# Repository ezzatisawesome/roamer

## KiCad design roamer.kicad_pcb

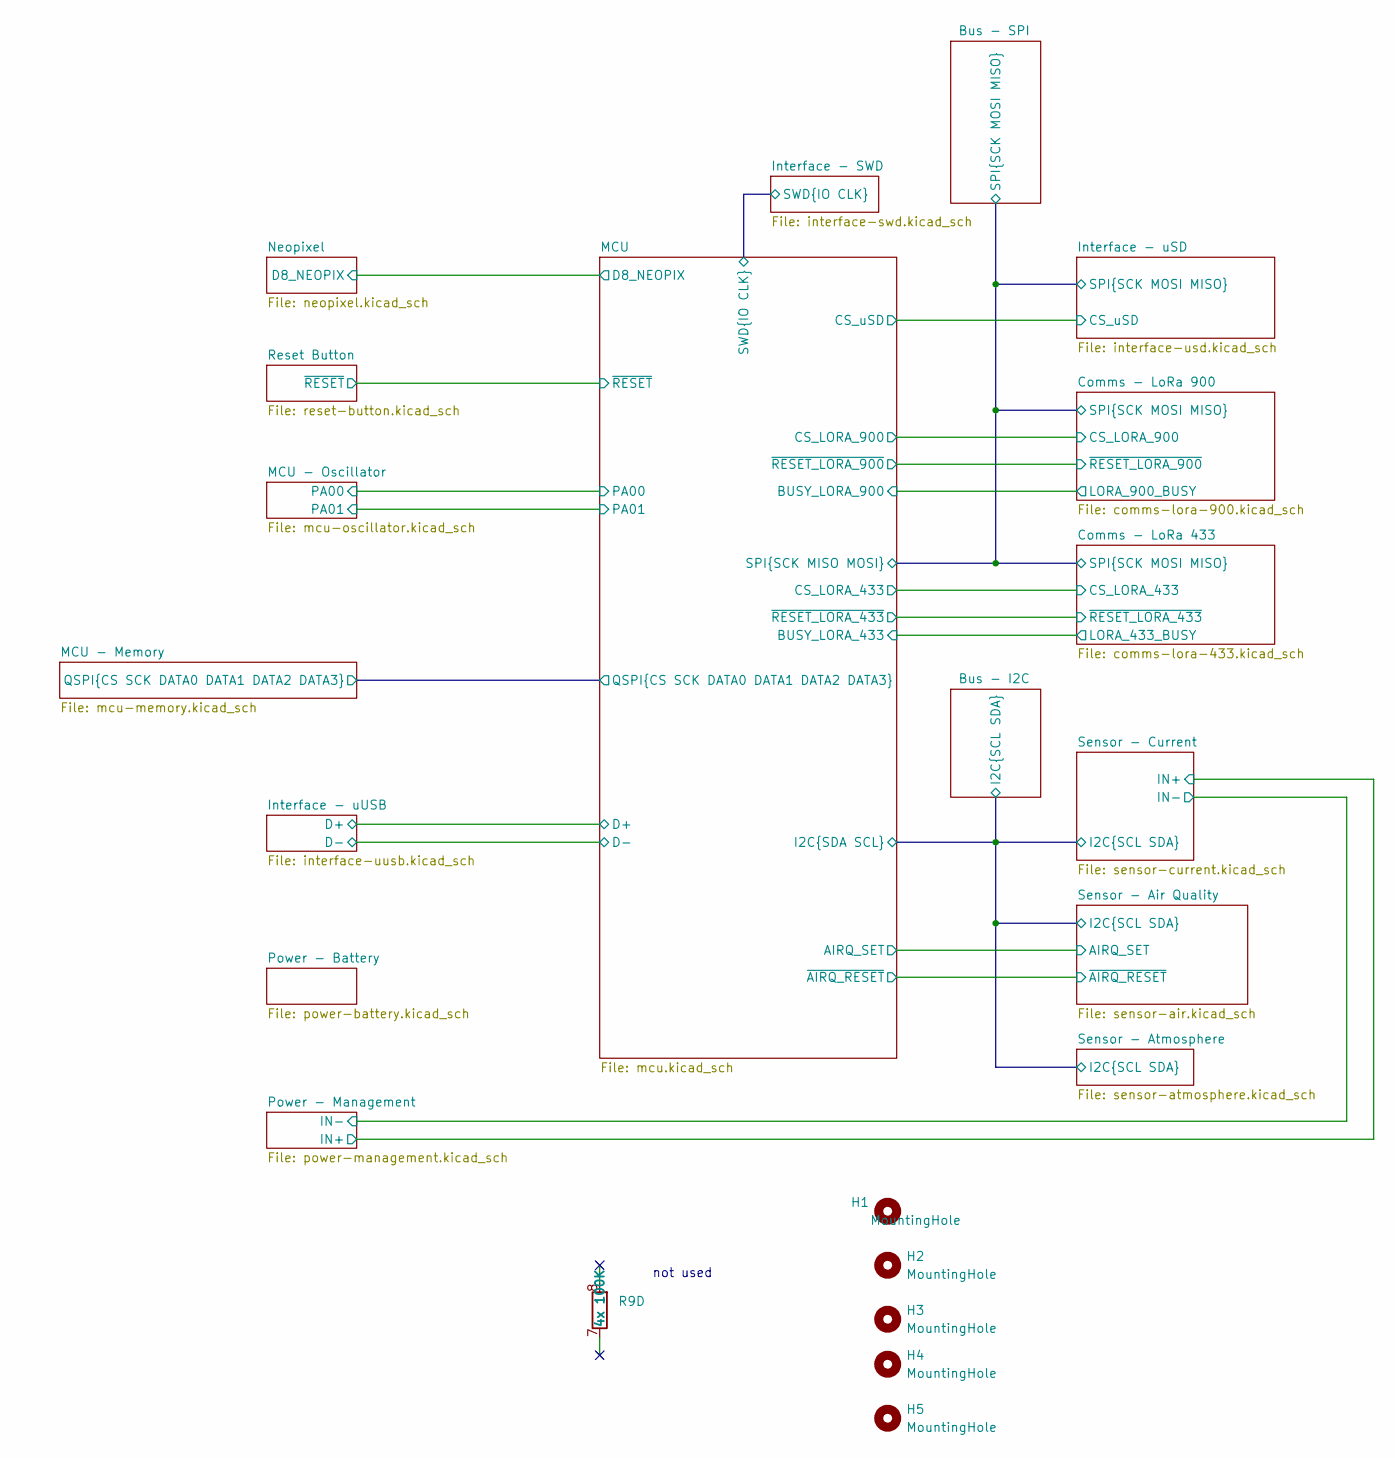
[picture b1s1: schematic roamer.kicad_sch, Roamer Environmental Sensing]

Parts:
H1, H2, H3, H4, H5: MountingHole; MountingHole_2.2mm_M2_DIN965_Pad
R9: 4x 100K; R_Array_Convex_4x1206; Mfr P/N CAY16-1003F4LF

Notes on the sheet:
not used

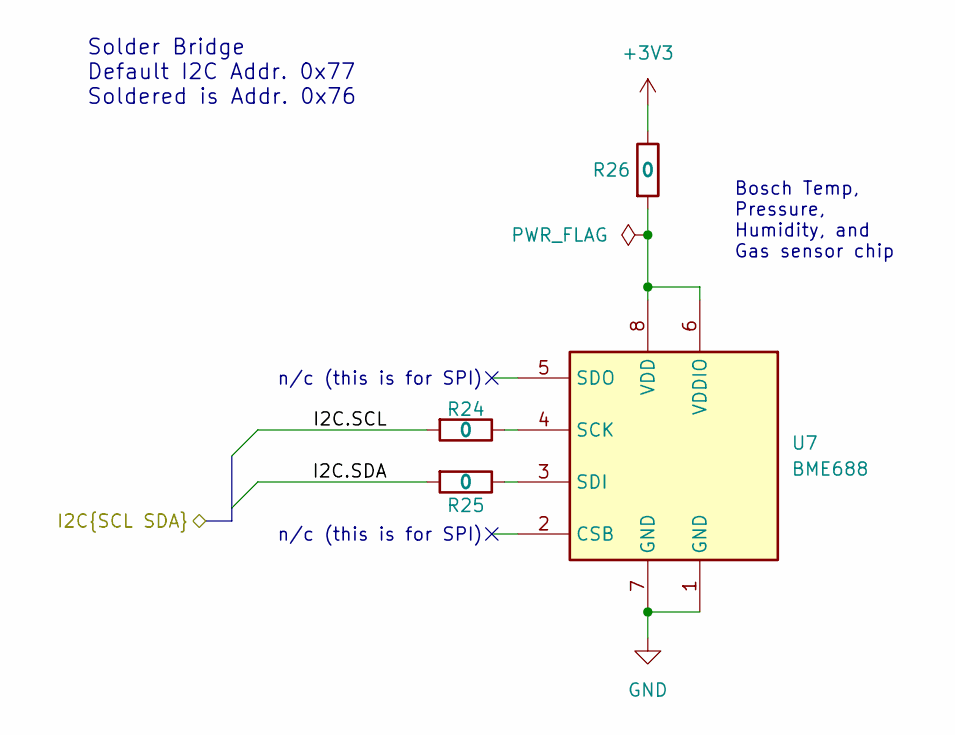
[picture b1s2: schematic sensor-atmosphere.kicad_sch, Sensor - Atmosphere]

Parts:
R24, R25, R26: 0; R_0603_1608Metric; Mfr P/N RC0603JR-070RL
U7: BME688; Bosch_LGA-8_3x3mm_P0.8mm_ClockwisePinNumbering; Mfr P/N BME688

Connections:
+3V3: R26.1; also elsewhere on the board
/Bus - I2C/I2C.SCL: R24.2; also elsewhere on the board
/Bus - I2C/I2C.SDA: R25.2; also elsewhere on the board
GND: U7.1 (GND), U7.7 (GND); also elsewhere on the board
unnamed: R24.1, U7.4 (SCK)
unnamed: R25.1, U7.3 (SDI)
unnamed: R26.2, U7.6 (VDDIO), U7.8 (VDD)

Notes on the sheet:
n/c (this is for SPI)
Bosch Temp, Pressure, Humidity, and Gas sensor chip
Solder Bridge Default I2C Addr. 0x77 Soldered is Addr. 0x76

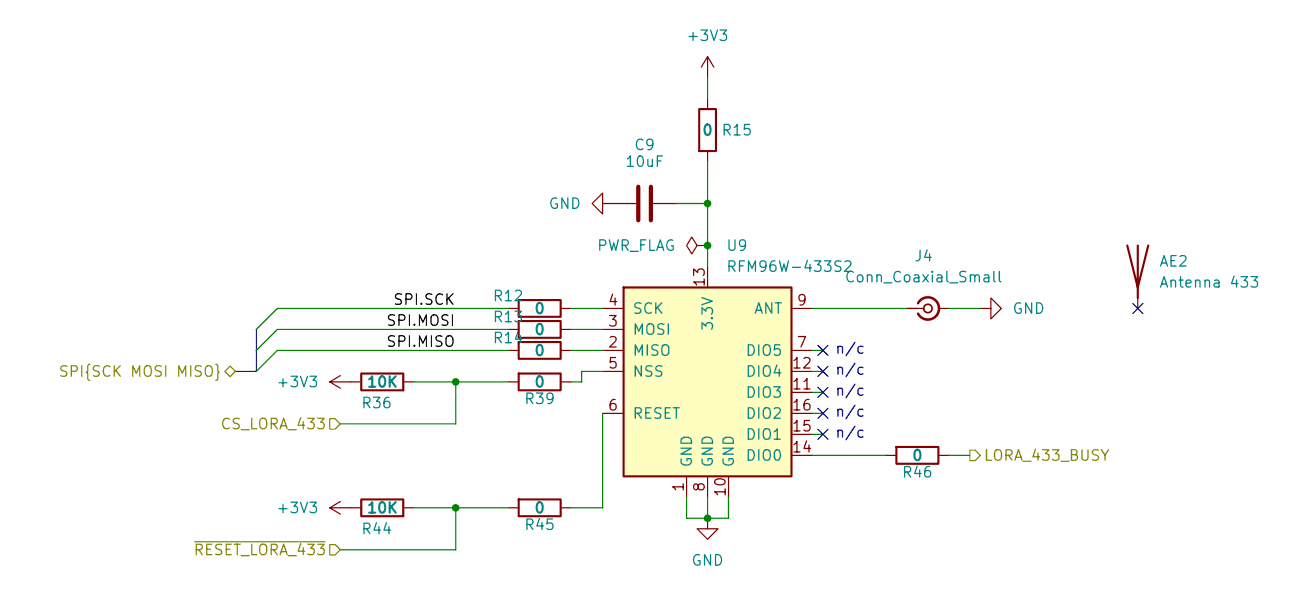
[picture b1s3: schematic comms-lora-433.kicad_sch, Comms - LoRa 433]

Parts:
AE2: Antenna 433; Mfr P/N ANT-433-PW-QW-UFL
C9: 10uF; L_0805_2012Metric; Mfr P/N CL21A106KOQNNNE
J4: Conn_Coaxial_Small; U.FL_Molex_MCRF_73412-0110_Vertical; Mfr P/N 0734120110
R12, R13, R14, R15, R39, R45, R46: 0; R_0603_1608Metric; Mfr P/N RC0603JR-070RL
R36, R44: 10K; R_0603_1608Metric; Mfr P/N RNCP0603FTD10K0
U9: RFM96W-433S2; HOPERF_RFM9XW_SMD; Mfr P/N 3073

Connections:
+3V3: R15.1, R36.1, R44.1; also elsewhere on the board
/Bus - SPI/SPI.MISO: R14.2; also elsewhere on the board
/Bus - SPI/SPI.MOSI: R13.2; also elsewhere on the board
/Bus - SPI/SPI.SCK: R12.2; also elsewhere on the board
/Comms - LoRa 433/CS_LORA_433: R36.2, R39.2; also elsewhere on the board
/Comms - LoRa 433/LORA_433_BUSY: R46.1; also elsewhere on the board
/Comms - LoRa 433/~RESET_LORA_433: R44.2, R45.2; also elsewhere on the board
GND: C9.1, J4.2 (Ext), U9.1 (GND), U9.8 (GND), U9.10 (GND); also elsewhere on the board
unnamed: J4.1 (In), U9.9 (ANT)
unnamed: C9.2, R15.2, U9.13 (3.3V)
unnamed: R46.2, U9.14 (DIO0)
unnamed: R14.1, U9.2 (MISO)
unnamed: R13.1, U9.3 (MOSI)
unnamed: R39.1, U9.5 (NSS)
unnamed: R45.1, U9.6 (RESET)
unnamed: R12.1, U9.4 (SCK)

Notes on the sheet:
n/c

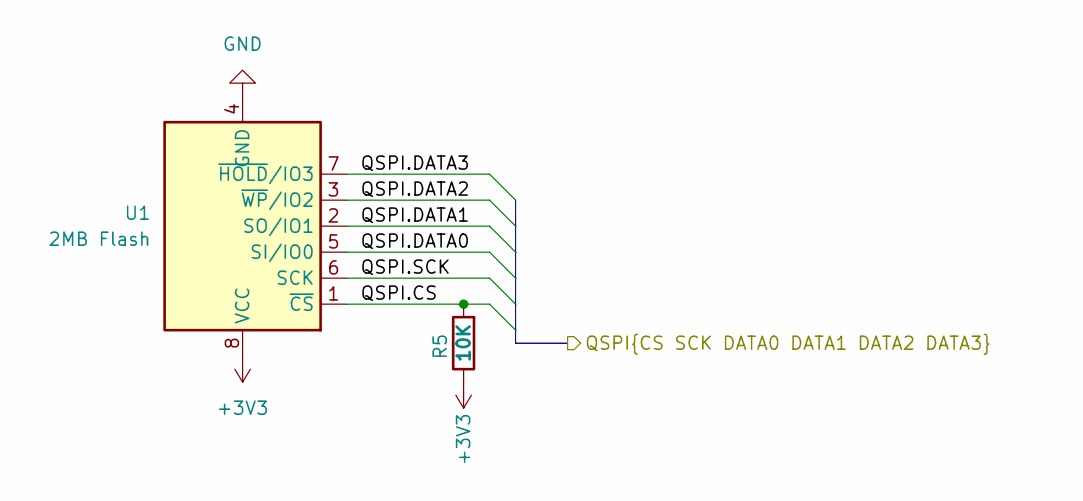
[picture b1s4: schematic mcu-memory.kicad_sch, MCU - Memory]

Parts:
R5: 10K; R_0603_1608Metric; Mfr P/N RNCP0603FTD10K0
U1: 2MB Flash; SOIC-8_3.9x4.9mm_P1.27mm; Mfr P/N GD25Q16ETIGR

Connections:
+3V3: R5.1, U1.8 (VCC); also elsewhere on the board
/MCU - Memory/QSPI.CS: R5.2, U1.1 (~CS); also elsewhere on the board
/MCU - Memory/QSPI.DATA0: U1.5 (SI/IO0); also elsewhere on the board
/MCU - Memory/QSPI.DATA1: U1.2 (SO/IO1); also elsewhere on the board
/MCU - Memory/QSPI.DATA2: U1.3 (~WP/IO2); also elsewhere on the board
/MCU - Memory/QSPI.DATA3: U1.7 (~HOLD/IO3); also elsewhere on the board
/MCU - Memory/QSPI.SCK: U1.6 (SCK); also elsewhere on the board
GND: U1.4 (GND); also elsewhere on the board

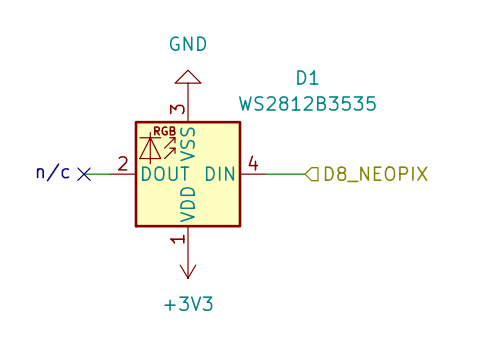
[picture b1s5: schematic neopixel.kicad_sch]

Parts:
D1: WS2812B3535; LED_SK6812MINI_PLCC4_3.5x3.5mm_P1.75mm; Mfr P/N SK6812MINI

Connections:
+3V3: D1.1 (VDD); also elsewhere on the board
/MCU/D8_NEOPIX: D1.4 (DIN); also elsewhere on the board
GND: D1.3 (VSS); also elsewhere on the board

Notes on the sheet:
n/c

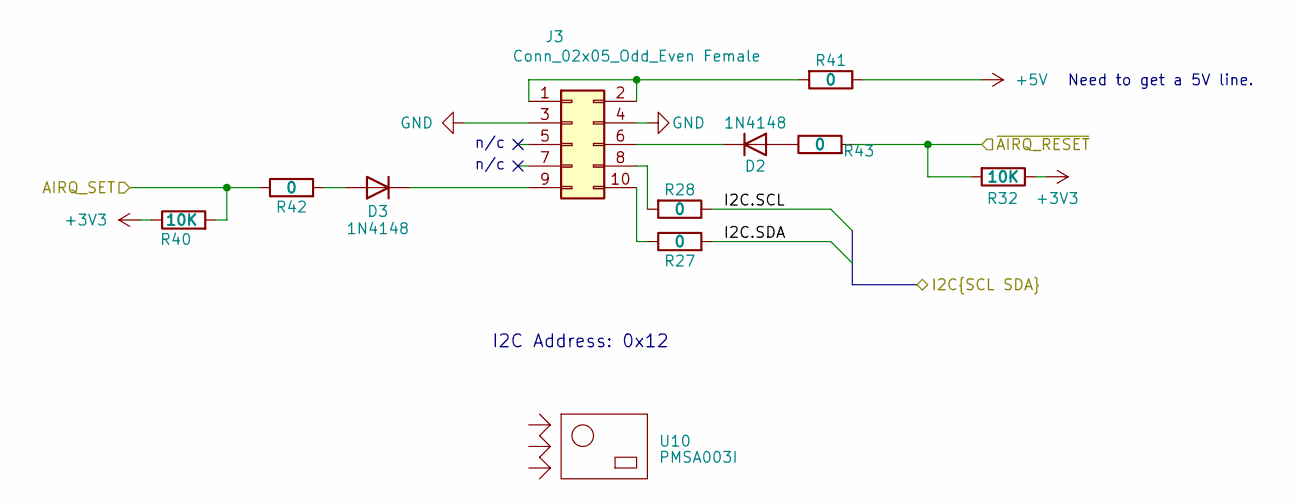
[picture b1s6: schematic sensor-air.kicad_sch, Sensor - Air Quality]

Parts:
D2, D3: 1N4148; D_SOD-323F; Mfr P/N 1N4148WX-TP
J3: Conn_02x05_Odd_Even Female; PinHeader_2x05_P1.27mm_Vertical_SMD; Mfr P/N 20021321-00010C4LF
R27, R28, R41, R42, R43: 0; R_0603_1608Metric; Mfr P/N RC0603JR-070RL
R32, R40: 10K; R_0603_1608Metric; Mfr P/N RNCP0603FTD10K0
U10: PMSA003I; Mfr P/N ZIO-101962

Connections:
+3V3: R32.1, R40.1; also elsewhere on the board
+5V: R41.1; also elsewhere on the board
/Bus - I2C/I2C.SCL: R28.1; also elsewhere on the board
/Bus - I2C/I2C.SDA: R27.2; also elsewhere on the board
/MCU/AIRQ_SET: R40.2, R42.1; also elsewhere on the board
/MCU/~AIRQ_RESET: R32.2, R43.2; also elsewhere on the board
GND: J3.3, J3.4; also elsewhere on the board
unnamed: D2.2 (A), R43.1
unnamed: D2.1 (K), J3.6
unnamed: D3.2 (A), R42.2
unnamed: D3.1 (K), J3.9
unnamed: J3.1, J3.2, R41.2
unnamed: J3.8, R28.2
unnamed: J3.10, R27.1

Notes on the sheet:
n/c
Need to get a 5V line.
I2C Address: 0x12

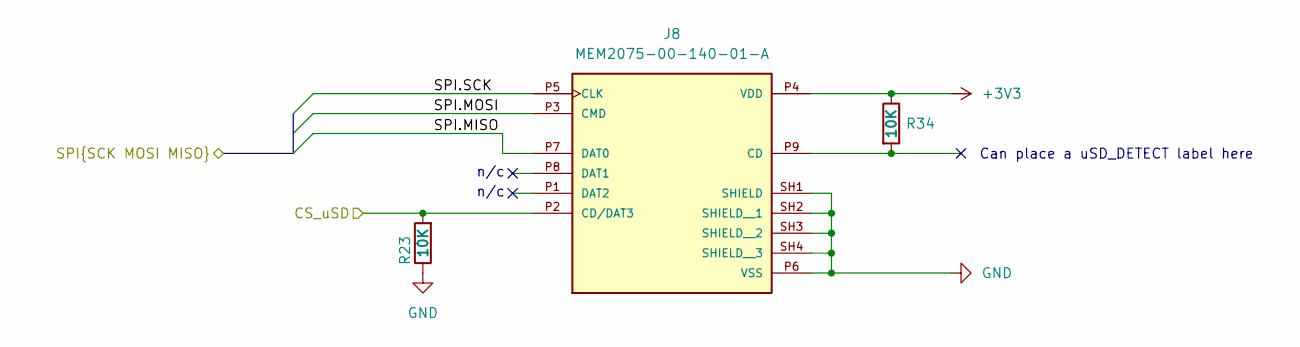
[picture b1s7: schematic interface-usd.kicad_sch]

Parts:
J8: MEM2075-00-140-01-A; GCT_MEM2075-00-140-01-A; PARTREV A
R23, R34: 10K; R_0603_1608Metric; Mfr P/N RNCP0603FTD10K0

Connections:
+3V3: J8.P4 (VDD), R34.1; also elsewhere on the board
/Bus - SPI/SPI.MISO: J8.P7 (DAT0); also elsewhere on the board
/Bus - SPI/SPI.MOSI: J8.P3 (CMD); also elsewhere on the board
/Bus - SPI/SPI.SCK: J8.P5 (CLK); also elsewhere on the board
/Interface - uSD/CS_uSD: J8.P2 (CD/DAT3), R23.2; also elsewhere on the board
GND: J8.P6 (VSS), J8.SH1 (SHIELD), J8.SH2 (SHIELD__1), J8.SH3 (SHIELD__2), J8.SH4 (SHIELD__3), R23.1; also elsewhere on the board

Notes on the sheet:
Can place a uSD_DETECT label here
n/c

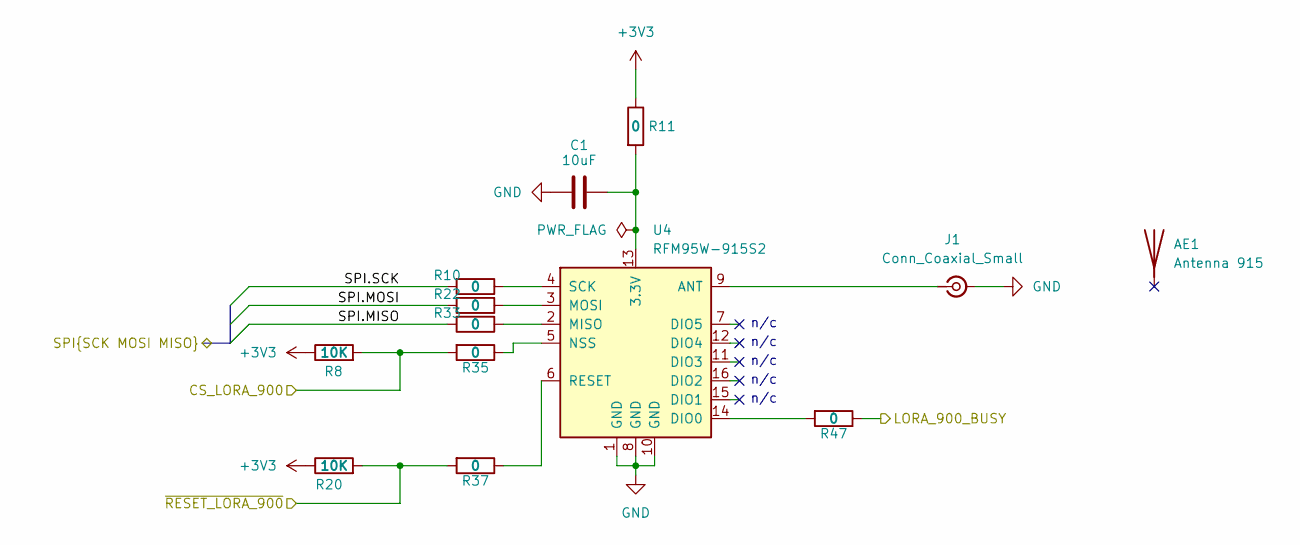
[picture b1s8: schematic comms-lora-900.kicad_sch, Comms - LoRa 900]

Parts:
AE1: Antenna 915; Mfr P/N ANT-916-PW-QW-UFL
C1: 10uF; L_0805_2012Metric; Mfr P/N CL21A106KOQNNNE
J1: Conn_Coaxial_Small; U.FL_Molex_MCRF_73412-0110_Vertical; Mfr P/N 0734120110
R8, R20: 10K; R_0603_1608Metric; Mfr P/N RNCP0603FTD10K0
R10, R11, R22, R33, R35, R37, R47: 0; R_0603_1608Metric; Mfr P/N RC0603JR-070RL
U4: RFM95W-915S2; HOPERF_RFM9XW_SMD; Mfr P/N 3072

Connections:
+3V3: R8.1, R11.1, R20.1; also elsewhere on the board
/Bus - SPI/SPI.MISO: R33.2; also elsewhere on the board
/Bus - SPI/SPI.MOSI: R22.2; also elsewhere on the board
/Bus - SPI/SPI.SCK: R10.2; also elsewhere on the board
/Comms - LoRa 900/CS_LORA_900: R8.2, R35.2; also elsewhere on the board
/Comms - LoRa 900/LORA_900_BUSY: R47.1; also elsewhere on the board
/Comms - LoRa 900/~RESET_LORA_900: R20.2, R37.2; also elsewhere on the board
GND: C1.1, J1.2 (Ext), U4.1 (GND), U4.8 (GND), U4.10 (GND); also elsewhere on the board
unnamed: J1.1 (In), U4.9 (ANT)
unnamed: C1.2, R11.2, U4.13 (3.3V)
unnamed: R47.2, U4.14 (DIO0)
unnamed: R33.1, U4.2 (MISO)
unnamed: R22.1, U4.3 (MOSI)
unnamed: R35.1, U4.5 (NSS)
unnamed: R37.1, U4.6 (RESET)
unnamed: R10.1, U4.4 (SCK)

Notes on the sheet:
n/c

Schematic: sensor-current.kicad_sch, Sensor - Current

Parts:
C19: 1uF; C_0603_1608Metric; Mfr P/N CC0603KRX7R7BB105
R16, R17, R18, R19, R21: 0; R_0603_1608Metric; Mfr P/N RC0603JR-070RL
U8: INA260; TSSOP-16_4.4x5mm_P0.65mm; Mfr P/N INA260AIPWR

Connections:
+3V3: R18.2; also elsewhere on the board
+BATT: R19.2; also elsewhere on the board
/Bus - I2C/I2C.SCL: R16.1; also elsewhere on the board
/Bus - I2C/I2C.SDA: R17.1; also elsewhere on the board
/Power - Management/IN-: R21.2; also elsewhere on the board
GND: C19.2, U8.6 (GND), U8.11 (GND); also elsewhere on the board
unnamed: R21.1, U8.14 (IN-), U8.15 (IN-), U8.16 (IN-)
unnamed: R16.2, U8.9 (SCL)
unnamed: R17.2, U8.8 (SDA)
unnamed: R19.1, U8.1 (IN+), U8.2 (IN+), U8.3 (IN+), U8.12 (VBUS)
unnamed: C19.1, R18.1, U8.10 (VS)

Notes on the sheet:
A1 A0 I2C Address (hex) GND GND 0x40(Default) GND VCC 0x41 VCC GND 0x44 VCC VCC 0x45
n/c

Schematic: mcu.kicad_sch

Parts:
C13: 10uF; L_0805_2012Metric; Mfr P/N CL21A106KOQNNNE
C14, C15: 1uF; C_0603_1608Metric; Mfr P/N CC0603KRX7R7BB105
JP1: SolderJumper_2_Open; SolderJumper-2_P1.3mm_Open_TrianglePad1.0x1.5mm
L1: RED; LED_0805_2012Metric; Mfr P/N LTST-S220KRKT
L2: 10uH; L_1008_2520Metric; Mfr P/N LSQEA251818T100K
MCU1: ATSAMD51J19A-A; TQFP-64_10x10mm_P0.5mm; Mfr P/N ATSAMD51J19A-AUTCT-ND
R6: 10K; R_0603_1608Metric; Mfr P/N RNCP0603FTD10K0
R7: 2.2K; R_0603_1608Metric; Mfr P/N CRGH0603F2K2
R9: 4x 100K; R_Array_Convex_4x1206; Mfr P/N CAY16-1003F4LF

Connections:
+3V3: JP1.2 (B), MCU1.8 (VDDANA), MCU1.16 (PA07), MCU1.21 (VDDIOB), MCU1.34 (VDDIO), MCU1.48 (VDDIO), MCU1.56 (VDDIO), R6.1; also elsewhere on the board
+BATT: R9.2 (R1.2); also elsewhere on the board
/Bus - I2C/I2C.SCL: MCU1.30 (PA13); also elsewhere on the board
/Bus - I2C/I2C.SDA: MCU1.29 (PA12); also elsewhere on the board
/Bus - SPI/SPI.MISO: MCU1.49 (PB22); also elsewhere on the board
/Bus - SPI/SPI.MOSI: MCU1.50 (PB23); also elsewhere on the board
/Bus - SPI/SPI.SCK: MCU1.36 (PA17); also elsewhere on the board
/Comms - LoRa 433/CS_LORA_433: MCU1.35 (PA16); also elsewhere on the board
/Comms - LoRa 433/LORA_433_BUSY: MCU1.40 (PB17); also elsewhere on the board
/Comms - LoRa 433/~RESET_LORA_433: MCU1.41 (PA20); also elsewhere on the board
/Comms - LoRa 900/CS_LORA_900: MCU1.31 (PA14); also elsewhere on the board
/Comms - LoRa 900/LORA_900_BUSY: MCU1.39 (PB16); also elsewhere on the board
/Comms - LoRa 900/~RESET_LORA_900: MCU1.38 (PA19); also elsewhere on the board
/Interface - SWD/SWD.CLK: MCU1.57 (PA30), R6.2; also elsewhere on the board
/Interface - SWD/SWD.IO: MCU1.58 (PA31); also elsewhere on the board
/Interface - uSD/CS_uSD: MCU1.37 (PA18); also elsewhere on the board
/Interface - uUSB/D+: MCU1.46 (PA25); also elsewhere on the board
/Interface - uUSB/D-: MCU1.45 (PA24); also elsewhere on the board
/MCU - Memory/QSPI.CS: MCU1.24 (PB11); also elsewhere on the board
/MCU - Memory/QSPI.DATA0: MCU1.17 (PA08); also elsewhere on the board
/MCU - Memory/QSPI.DATA1: MCU1.18 (PA09); also elsewhere on the board
/MCU - Memory/QSPI.DATA2: MCU1.19 (PA10); also elsewhere on the board
/MCU - Memory/QSPI.DATA3: MCU1.20 (PA11); also elsewhere on the board
/MCU - Memory/QSPI.SCK: MCU1.23 (PB10); also elsewhere on the board
/MCU - Oscillator/PA00: MCU1.1 (PA00); also elsewhere on the board
/MCU - Oscillator/PA01: MCU1.2 (PA01); also elsewhere on the board
/MCU/AIRQ_SET: MCU1.43 (PA22); also elsewhere on the board
/MCU/AREF: C14.1, JP1.1 (A), MCU1.4 (PA03); also elsewhere on the board
/MCU/D8_NEOPIX: MCU1.64 (PB03); also elsewhere on the board
/MCU/~AIRQ_RESET: MCU1.42 (PA21); also elsewhere on the board
/MCU/~RESET: MCU1.52 (~RESET); also elsewhere on the board
GND: C13.2, C14.2, C15.1, L1.1 (K), MCU1.7 (GNDANA), MCU1.22 (GND), MCU1.33 (GND), MCU1.47 (GND), MCU1.54 (GND), R9.3 (R2.1); also elsewhere on the board
unnamed: L1.2 (A), R7.1
unnamed: MCU1.44 (PA23), R7.2
unnamed: MCU1.62 (PB01), R9.1 (R1.1), R9.4 (R2.2)
unnamed: L2.2, MCU1.53 (VDDCORE)
unnamed: C13.1, C15.2, L2.1, MCU1.55 (VSW)

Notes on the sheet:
n/c
SWD PORT
RED INDICATOR LED

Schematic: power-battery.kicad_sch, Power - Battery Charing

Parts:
C3: 10uF; L_0805_2012Metric; Mfr P/N CL21A106KOQNNNE
CHG1: ORANGE; LED_0805_2012Metric; Mfr P/N B1701UD--20D000414U1930
J2: JSTPH; JST_PH_S2B-PH-SM4-TB_1x02-1MP_P2.00mm_Horizontal; Mfr P/N S2B-PH-SM4-TB
R2: 1K; C_0603_1608Metric; Mfr P/N MCT06030C1001FP500
R4: 10K; R_0603_1608Metric; Mfr P/N RNCP0603FTD10K0
U3: MCP73831-2-OT; SOT-23-5; Mfr P/N MCP73831T-2ATI/OT

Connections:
+BATT: C3.1, J2.1, U3.3 (V_{BAT}); also elsewhere on the board
GND: C3.2, J2.2, R4.1, U3.2 (V_{SS}); also elsewhere on the board
unnamed: CHG1.1 (K), R2.2
unnamed: R4.2, U3.5 (PROG)
unnamed: R2.1, U3.1 (STAT)
VBUS: CHG1.2 (A), U3.4 (V_{DD}); also elsewhere on the board

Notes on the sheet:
10K = 100mA 5.0K = 200mA 2.0K = 500mA 1.0K = 1000mA
ORGANGE CHARGING INDICATOR LED

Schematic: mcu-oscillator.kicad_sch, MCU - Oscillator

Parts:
C2, C4: 22pF; C_0603_1608Metric; Mfr P/N C0603C220K4GAC7867
X2: 32.768 kHz; Crystal_SMD_3215-2Pin_3.2x1.5mm; Mfr P/N STDMUA17-32.768K

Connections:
/MCU - Oscillator/PA00: C4.1, X2.1; also elsewhere on the board
/MCU - Oscillator/PA01: C2.1, X2.2; also elsewhere on the board
GND: C2.2, C4.2; also elsewhere on the board

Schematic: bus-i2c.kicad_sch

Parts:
R30, R31: 10K; R_0603_1608Metric; Mfr P/N RNCP0603FTD10K0

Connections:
+3V3: R30.1, R31.1; also elsewhere on the board
/Bus - I2C/I2C.SCL: R31.2; also elsewhere on the board
/Bus - I2C/I2C.SDA: R30.2; also elsewhere on the board

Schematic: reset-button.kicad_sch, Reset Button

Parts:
C12: 1uF; C_0603_1608Metric; Mfr P/N CC0603KRX7R7BB105
R1: 10K; R_0603_1608Metric; Mfr P/N RNCP0603FTD10K0
SW1: KMR2; SW_Push_1P1T_NO_CK_KMR2; Mfr P/N KM241NG ULC LFS

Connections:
+3V3: R1.2; also elsewhere on the board
/MCU/~RESET: C12.1, R1.1, SW1.2; also elsewhere on the board
GND: C12.2, SW1.1; also elsewhere on the board

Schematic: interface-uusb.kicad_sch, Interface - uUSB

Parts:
TP3: D+ Testpoint; TestPoint_Pad_D1.0mm
TP4: D- TestPoint; TestPoint_Pad_D1.0mm
X3: microUSB 2.0 B; USB_Micro-B_Amphenol_10118194_Horizontal; Mfr P/N 10118194-0001LF

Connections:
/Interface - uUSB/D+: TP3.1, X3.3 (D+); also elsewhere on the board
/Interface - uUSB/D-: TP4.1, X3.2 (D-); also elsewhere on the board
GND: X3.5 (GND), X3.6 (Shield); also elsewhere on the board
VBUS: X3.1 (VBUS); also elsewhere on the board

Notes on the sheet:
n/c

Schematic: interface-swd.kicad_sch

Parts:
J5: Conn_02x05_Odd_Even Male; PinHeader_2x05_P1.27mm_Vertical_SMD; Mfr P/N 3220-10-0300-00

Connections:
+3V3: J5.1; also elsewhere on the board
/Interface - SWD/Key: J5.7
/Interface - SWD/SWD.CLK: J5.4; also elsewhere on the board
/Interface - SWD/SWD.IO: J5.2; also elsewhere on the board
/Interface - SWD/SWO: J5.6
/Interface - SWD/n/c: J5.8
/Interface - SWD/~RST: J5.10
GND: J5.3, J5.5, J5.9; also elsewhere on the board

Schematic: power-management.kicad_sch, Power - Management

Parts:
C5, C6, C8, C16, C17: 10uF; L_0805_2012Metric; Mfr P/N CL21A106KOQNNNE
C7, C10, C11, C18: 1uF; C_0603_1608Metric; Mfr P/N CC0603KRX7R7BB105
D4: MBR120; D_SOD-123; Mfr P/N MBR120LSFT1G
JP3: SolderJumper_2_Open; SolderJumper-2_P1.3mm_Open_TrianglePad1.0x1.5mm
Q3: DMP2070UQ-7; TSOT-23; Mfr P/N DMP2070UQ-7
R3: 10K; R_0603_1608Metric; Mfr P/N RNCP0603FTD10K0
R9: 4x 100K; R_Array_Convex_4x1206; Mfr P/N CAY16-1003F4LF
R38: 100K; R_0805_2012Metric; Mfr P/N RC0805FR-07100KL
TP1: VBUS Testpoint; TestPoint_Loop_D2.50mm_Drill1.0mm; Mfr P/N 5001
TP2: Batt Testpoint; TestPoint_Loop_D2.50mm_Drill1.0mm; Mfr P/N 5001
TP5: 5V Testpoint; TestPoint_Loop_D2.50mm_Drill1.0mm; Mfr P/N 5001
TP6: GND Testpoint; TestPoint_Loop_D2.50mm_Drill1.0mm; Mfr P/N 5001
TP7: 3V3 Testpoint; TestPoint_Loop_D2.50mm_Drill1.0mm; Mfr P/N 5001
U2: AP2112K-3.3; SOT-23-5; Mfr P/N AP2112K-3.3TRG1
U6: AP3602AKTR-G1; SOT-23-6_DIO; Mfr P/N AP3602AKTR-G1

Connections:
+3V3: C5.1, C7.1, C8.1, C10.2, C11.2, TP7.1, U2.5 (VOUT); also elsewhere on the board
+5V: C16.1, TP5.1, U6.1 (VOUT); also elsewhere on the board
/Power - Management/IN-: JP3.1 (A), Q3.1 (D); also elsewhere on the board
/Power - Management/POWER_IN: C6.1, C17.1, D4.1 (K), Q3.3 (S), R3.1, R38.2, U2.1 (VIN), U6.5 (VIN)
GND: C5.2, C6.2, C7.2, C8.2, C10.1, C11.1, C16.2, C17.2, R9.5 (R3.1), TP6.1, U2.2 (GND), U6.2 (GND); also elsewhere on the board
unnamed: JP3.2 (B), TP2.1
unnamed: R3.2, U2.3 (EN)
unnamed: R38.1, U6.3 (*SHDN)
unnamed: C18.2, U6.6 (C+)
unnamed: C18.1, U6.4 (C-)
VBUS: D4.2 (A), Q3.2 (G), R9.6 (R3.2), TP1.1; also elsewhere on the board

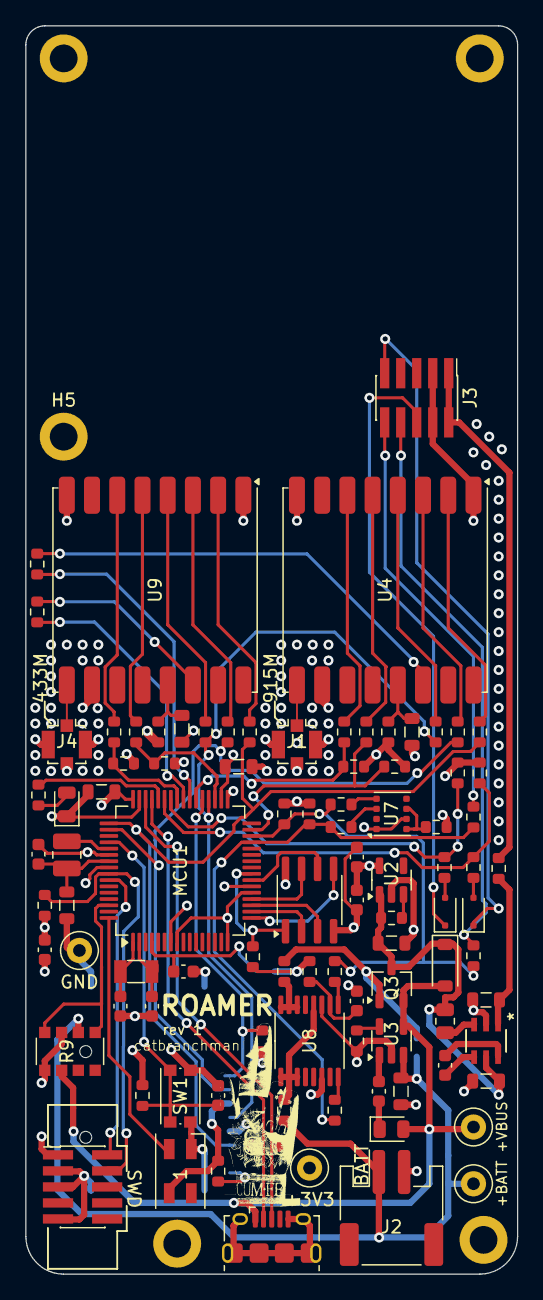
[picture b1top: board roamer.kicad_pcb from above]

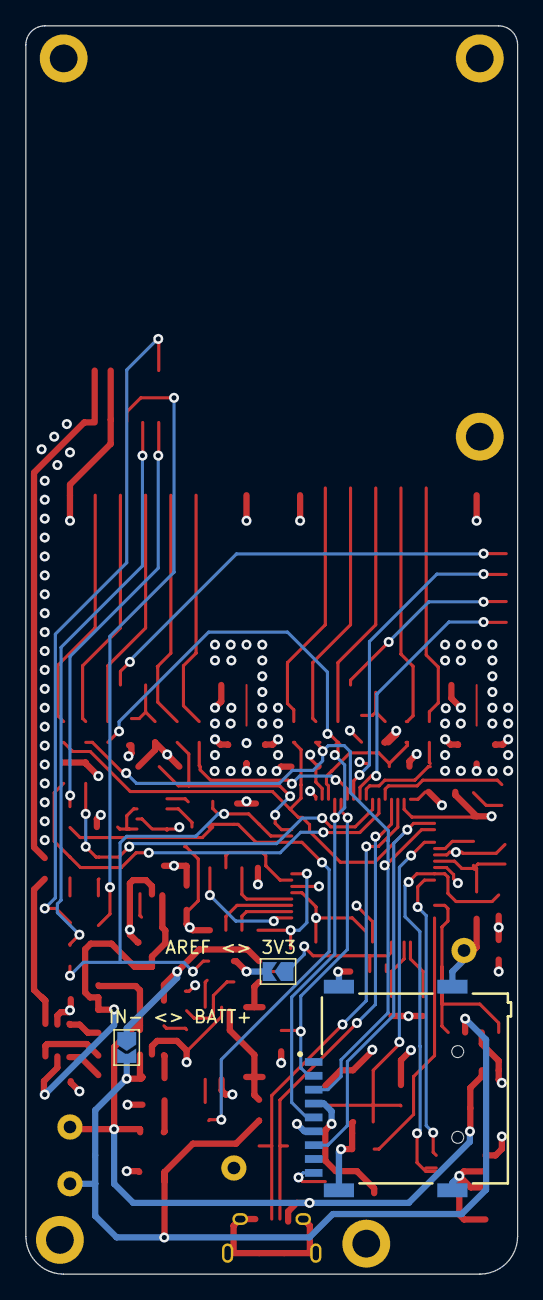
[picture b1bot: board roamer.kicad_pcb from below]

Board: 4 copper layers, 39.0 x 99.0 mm, 104 parts (3 on the bottom side), 79 nets.

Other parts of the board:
+3V3: 3V3 Testpoint; TestPoint_Loop_D2.50mm_Drill1.0mm
+BATT: Batt Testpoint; TestPoint_Loop_D2.50mm_Drill1.0mm
+VBUS: VBUS Testpoint; TestPoint_Loop_D2.50mm_Drill1.0mm
AREF <> 3V3: SolderJumper_2_Open; SolderJumper-2_P1.3mm_Open_TrianglePad1.0x1.5mm
GND: GND Testpoint; TestPoint_Loop_D2.50mm_Drill1.0mm
IN- <> BATT+: SolderJumper_2_Open; SolderJumper-2_P1.3mm_Open_TrianglePad1.0x1.5mm

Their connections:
+3V3: +3V3.1, AREF <> 3V3.2 (B); also elsewhere on the board
+BATT: +BATT.1, IN- <> BATT+.2 (B); also elsewhere on the board
/MCU/AREF: AREF <> 3V3.1 (A); also elsewhere on the board
/Power - Management/IN-: IN- <> BATT+.1 (A); also elsewhere on the board
GND: GND.1; also elsewhere on the board
VBUS: +VBUS.1; also elsewhere on the board

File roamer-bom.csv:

"Reference","Value","Datasheet","Footprint","Qty","DNP"
"AE1","Antenna 915","RF ANT 916MHZ WHIP STR CAB PAN","","1",""
"AE2","Antenna 433","Datasheet","","1",""
"C1,C3,C5,C6,C8,C9,C13,C16,C17","10uF","https://mm.digikey.com/Volume0/opasdata/d220001/medias/docus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","Inductor_SMD:L_0805_2012Metric","9",""
"C2,C4","22pF","https://content.kemet.com/datasheets/KEM_C1003_COG_SMD.pdf","Capacitor_SMD:C_0603_1608Metric","2",""
"C7,C10,C11,C12,C14,C15,C18,C19","1uF","https://www.yageo.com/upload/media/product/productsearch/dat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","Capacitor_SMD:C_0603_1608Metric","8",""
"CHG1","ORANGE","https://mm.digikey.com/Volume0/opasdata/d220001/medias/docus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","LED_SMD:LED_0805_2012Metric","1",""
"D1","WS2812B3535","https://cdn-shop.adafruit.com/product-files/2686/SK6812MINI_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","LED_SMD:LED_SK6812MINI_PLCC4_3.5x3.5mm_P1.75mm","1",""
"D2,D3","1N4148","https://www.mccsemi.com/pdf/Products/1N4148WX(SOD-323).pdf","Diode_SMD:D_SOD-323F","2",""
"D4","MBR120","https://www.onsemi.com/pdf/datasheet/mbr120lsft1-d.pdf","Diode_SMD:D_SOD-123","1",""
"J1,J4","Conn_Coaxial_Small","https://www.molex.com/en-us/products/part-detail/734120110?d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","Connector_Coaxial:U.FL_Molex_MCRF_73412-0110_Vertical","2",""
"J2","JSTPH","https://www.jst-mfg.com/product/pdf/eng/ePH.pdf","Connector_JST:JST_PH_S2B-PH-SM4-TB_1x02-1MP_P2.00mm_Horizontal","1",""
"J3","Conn_02x05_Odd_Even Female","https://cdn.amphenol-cs.com/media/wysiwyg/files/documentatio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","Connector_PinHeader_1.27mm:PinHeader_2x05_P1.27mm_Vertical_SMD","1",""
"J5","Conn_02x05_Odd_Even Male","https://www.cnctech.us/pdfs/3220-XX-0300-00_.pdf","Connector_PinHeader_1.27mm:PinHeader_2x05_P1.27mm_Vertical_SMD","1",""
"J8","MEM2075-00-140-01-A","https://gct.co/files/specs/mem2075-spec.pdf","footprints:GCT_MEM2075-00-140-01-A","1",""
"L1","RED","https://optoelectronics.liteon.com/upload/download/DS22-2000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","LED_SMD:LED_0805_2012Metric","1",""
"L2","10uH","https://mm.digikey.com/Volume0/opasdata/d220001/medias/docus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","Inductor_SMD:L_1008_2520Metric","1",""
"MCU1","ATSAMD51J19A-A","http://ww1.microchip.com/downloads/en/DeviceDoc/60001507E.pdf","Package_QFP:TQFP-64_10x10mm_P0.5mm","1",""
"Q3","DMP2070UQ-7","https://ngspice.sourceforge.io/docs/ngspice-html-manual/manu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","Package_TO_SOT_SMD:TSOT-23","1",""
"R1,R3,R4,R5,R6,R8,R20,R23,R30,R31,R32,R34,R36,R40,R44","10K","https://www.seielect.com/catalog/sei-rncp.pdf","Resistor_SMD:R_0603_1608Metric","15",""
"R2","1K","https://www.vishay.com/docs/28705/mcx0x0xpro.pdf","Capacitor_SMD:C_0603_1608Metric","1",""
"R7","2.2K","https://www.te.com/usa-en/product-1-2176177-5.datasheet.pdf","Resistor_SMD:R_0603_1608Metric","1",""
"R9","4x 100K","https://www.bourns.com/docs/Product-Datasheets/CATCAY.pdf","Resistor_SMD:R_Array_Convex_4x1206","1",""
"R10,R11,R12,R13,R14,R15,R16,R17,R18,R19,R21,R22,R24,R25,R26,R27,R28,R33,R35,R37,R39,R41,R42,R43,R45,R46,R47","0","Datasheet","Resistor_SMD:R_0603_1608Metric","27",""
"R38","100K","https://www.yageo.com/upload/media/product/products/datashee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","Resistor_SMD:R_0805_2012Metric","1",""
"SW1","KMR2","https://www.ckswitches.com/media/1479/kmr2.pdf","Button_Switch_SMD:SW_Push_1P1T_NO_CK_KMR2","1",""
"TP1","VBUS Testpoint","https://www.keyelco.com/userAssets/file/M65p56.pdf","TestPoint:TestPoint_Loop_D2.50mm_Drill1.0mm","1",""
"TP2","Batt Testpoint","https://www.keyelco.com/userAssets/file/M65p56.pdf","TestPoint:TestPoint_Loop_D2.50mm_Drill1.0mm","1",""
"TP3","D+ Testpoint","~","TestPoint:TestPoint_Pad_D1.0mm","1",""
"TP4","D- TestPoint","~","TestPoint:TestPoint_Pad_D1.0mm","1",""
"TP5","5V Testpoint","https://www.keyelco.com/userAssets/file/M65p56.pdf","TestPoint:TestPoint_Loop_D2.50mm_Drill1.0mm","1",""
"TP6","GND Testpoint","https://www.keyelco.com/userAssets/file/M65p56.pdf","TestPoint:TestPoint_Loop_D2.50mm_Drill1.0mm","1",""
"TP7","3V3 Testpoint","https://www.keyelco.com/userAssets/file/M65p56.pdf","TestPoint:TestPoint_Loop_D2.50mm_Drill1.0mm","1",""
"U1","2MB Flash","https://www.gigadevice.com.cn/Public/Uploads/uploadfile/file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","Package_SO:SOIC-8_3.9x4.9mm_P1.27mm","1",""
"U2","AP2112K-3.3","https://www.diodes.com/assets/Datasheets/AP2112.pdf","Package_TO_SOT_SMD:SOT-23-5","1",""
"U3","MCP73831-2-OT","https://ww1.microchip.com/downloads/en/DeviceDoc/MCP73831-Fa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","Package_TO_SOT_SMD:SOT-23-5","1",""
"U4","RFM95W-915S2","https://www.hoperf.com/data/upload/portal/20181127/5bfcbea20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","RF_Module:HOPERF_RFM9XW_SMD","1",""
"U6","AP3602AKTR-G1","AP3602AKTR-G1","footprints:SOT-23-6_DIO","1",""
"U7","BME688","https://www.bosch-sensortec.com/media/boschsensortec/downloa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","Package_LGA:Bosch_LGA-8_3x3mm_P0.8mm_ClockwisePinNumbering","1",""
"U8","INA260","http://www.ti.com/lit/ds/symlink/ina260.pdf","Package_SO:TSSOP-16_4.4x5mm_P0.65mm","1",""
"U9","RFM96W-433S2","https://www.hoperf.com/data/upload/portal/20181127/5bfcc0ac6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","RF_Module:HOPERF_RFM9XW_SMD","1",""
"U10","PMSA003I","https://www.smart-prototyping.com/image/data/digikey/101962/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","","1",""
"X2","32.768 kHz","https://www.ndk.com/images/products/catalog/c_NX3215SE_e.pdf","Crystal:Crystal_SMD_3215-2Pin_3.2x1.5mm","1",""
"X3","microUSB 2.0 B","https://cdn.amphenol-cs.com/media/wysiwyg/files/documentatio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","Connector_USB:USB_Micro-B_Amphenol_10118194_Horizontal","1",""

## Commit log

2024-10-23 Added MCU power circuitry. Added LoRa module. Added BME680 circuitry.
2024-10-23 Adding I2C bus to circuit
2024-10-29 Adding symbols information
2024-10-29 Adding rest of schematic
2024-10-29 Fixing footprint imports
2024-10-30 Spamming 0 ohm resistors
2024-10-30 Adding more 0 ohm resistors and pullups for I2C lines
2024-10-30 Adding diodes for Air Quality Sensor SET and RESET pins
2024-10-30 Adding testpoints to I2C, SPI, and signals
2024-11-02 Fixing lots of ERC errors
2024-11-02 Starting layout
2024-11-03 Adding 5V boost
2024-11-03 Working on layout
2024-11-04 Layed out the radio and PMS00
2024-11-04 Working on layout still
2024-11-04 Getting there with the layout
2024-11-06 Redid board layout. Still have to add bypass caps
2024-11-07 Connected all signals except Buses
2024-11-07 Connected all signal lines
2024-11-07 Finished layout
2024-11-08 Added mounting holes
2024-11-12 Cleaning up traces
2024-11-12 Adding via shielding for UFL connectors
2024-11-12 Added via shielding for 5v line
2024-11-13 Adding finishing touches
2024-11-13 Creating fab package
2024-11-19 Updating silkscreen comments
2024-11-24 Updating tags
